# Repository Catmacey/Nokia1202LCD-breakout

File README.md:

Nokia 1202 LCD breakout board
=============================

This is a simple Break-out board for the LCD found in Nokia 1202 phones.
The LCD is B/W 96x68px and driven by a 9bit SPI. 
The LCD terminates in a 12 pin 0.6mm pitch flex connector. 
It's tiny but still within the bounds of hand soldering.

The board is modelled on the Sparkfun 5110 breakout and shares 
the same pin-out in order to drop into an existing project.

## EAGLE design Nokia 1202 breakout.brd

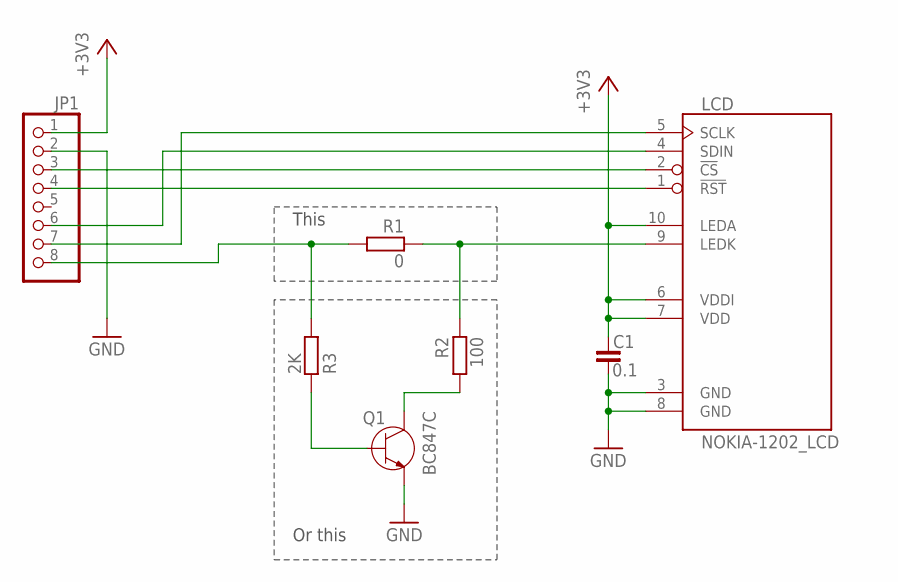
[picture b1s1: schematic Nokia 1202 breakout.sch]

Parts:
C1: 0.1; C0805
JP1: PINHD-1X8; 1X08
LCD: NOKIA-1202_LCD
Q1: BC847C; SOT23
R1: 0; R0805
R2: 100; R0805
R3: 2K; R0805

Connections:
+3V3: C1.1, JP1.1, LCD.6 (VDDI), LCD.7 (VDD), LCD.10 (LEDA)
BL: JP1.8, R1.2, R3.2
GND: C1.2, JP1.2, LCD.3 (GND), LCD.8 (GND), Q1.2 (E)
MOSI: JP1.6, LCD.4 (SDIN)
unnamed: JP1.3, LCD.2 (!CS)
unnamed: JP1.4, LCD.1 (!RST)
unnamed: LCD.9 (LEDK), R1.1, R2.1
unnamed: Q1.1 (B), R3.1
unnamed: Q1.3 (C), R2.2
SCLK: JP1.7, LCD.5 (SCLK)

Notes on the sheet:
This
Or this

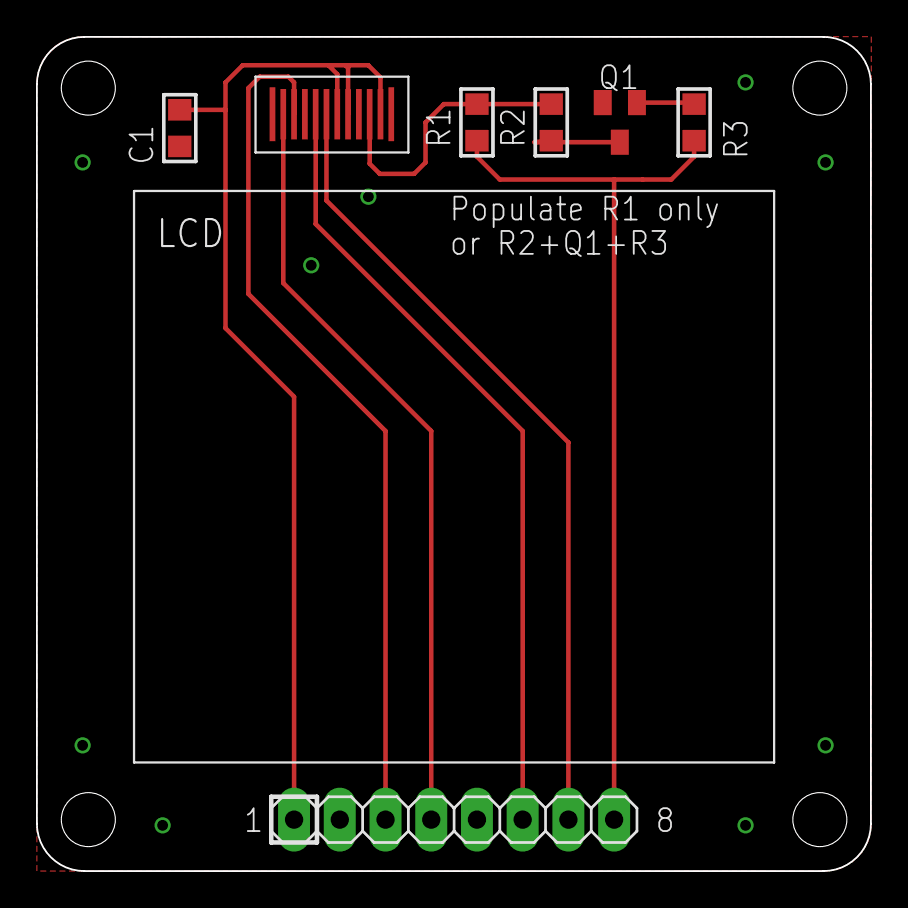
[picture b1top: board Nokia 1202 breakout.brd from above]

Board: 2 copper layers, 46.3 x 46.3 mm, 7 parts (0 on the bottom side), 10 nets.

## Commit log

2013-07-26 Initial import
2014-02-21 Adde
